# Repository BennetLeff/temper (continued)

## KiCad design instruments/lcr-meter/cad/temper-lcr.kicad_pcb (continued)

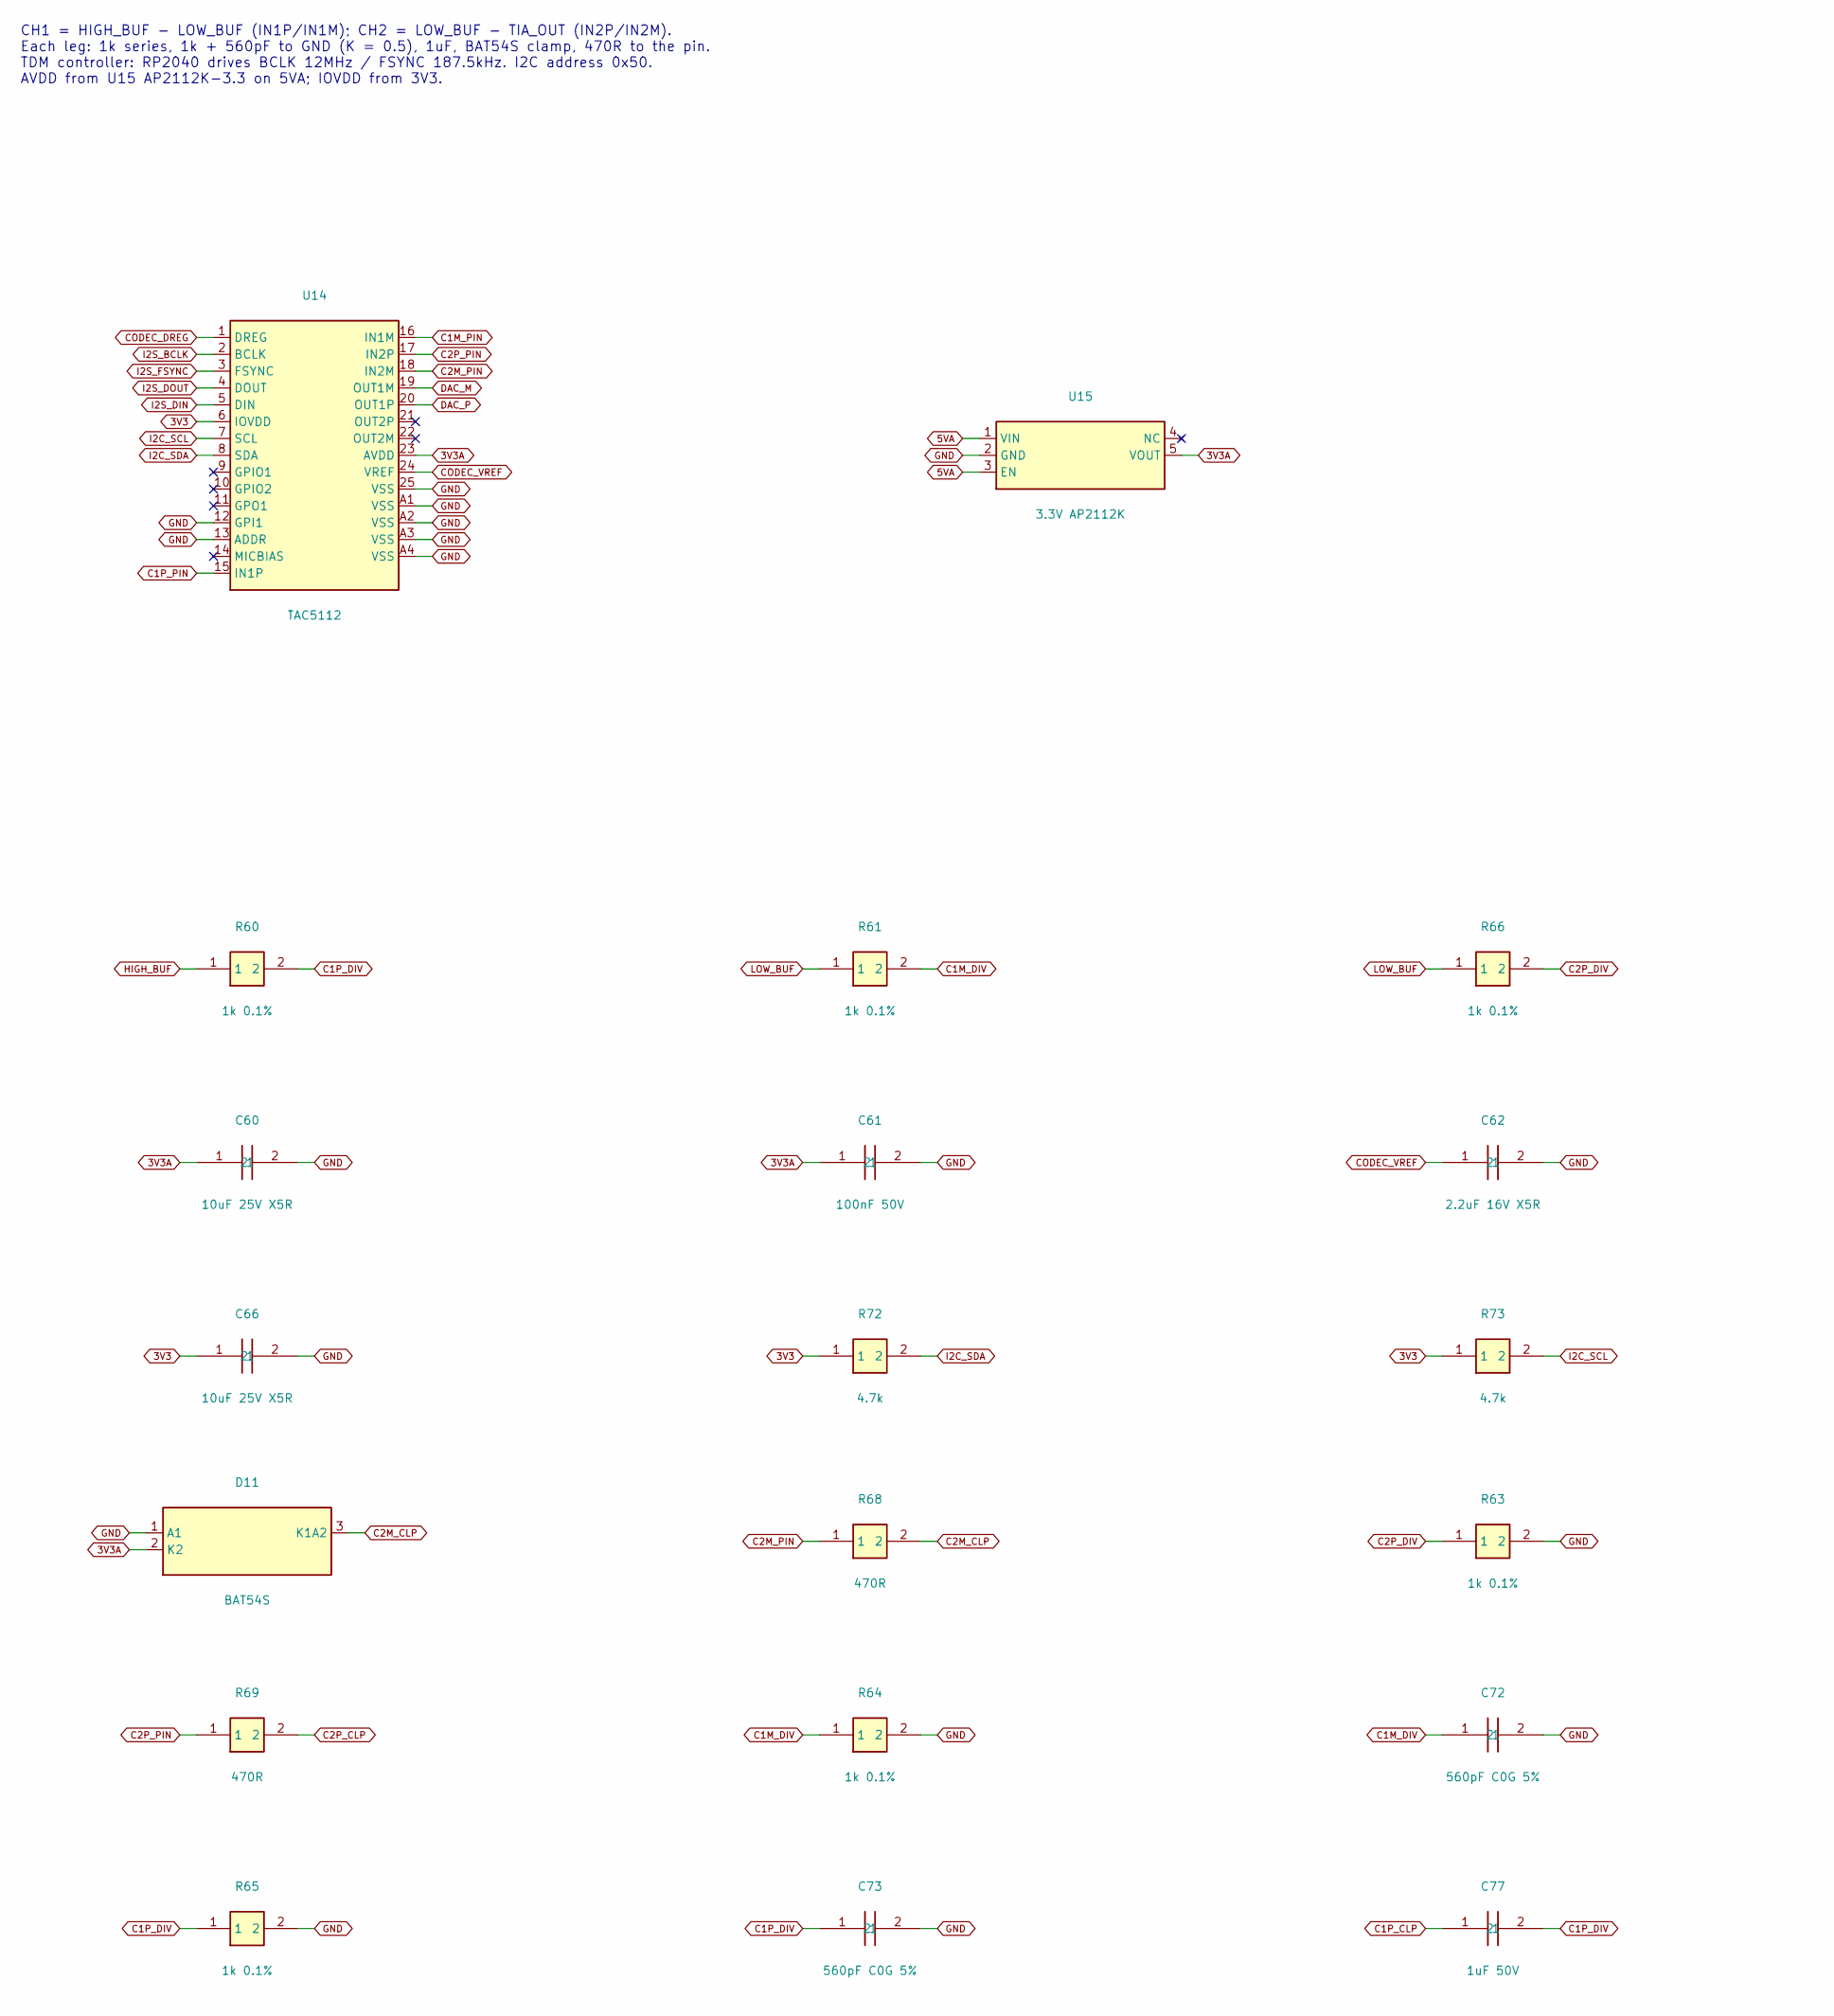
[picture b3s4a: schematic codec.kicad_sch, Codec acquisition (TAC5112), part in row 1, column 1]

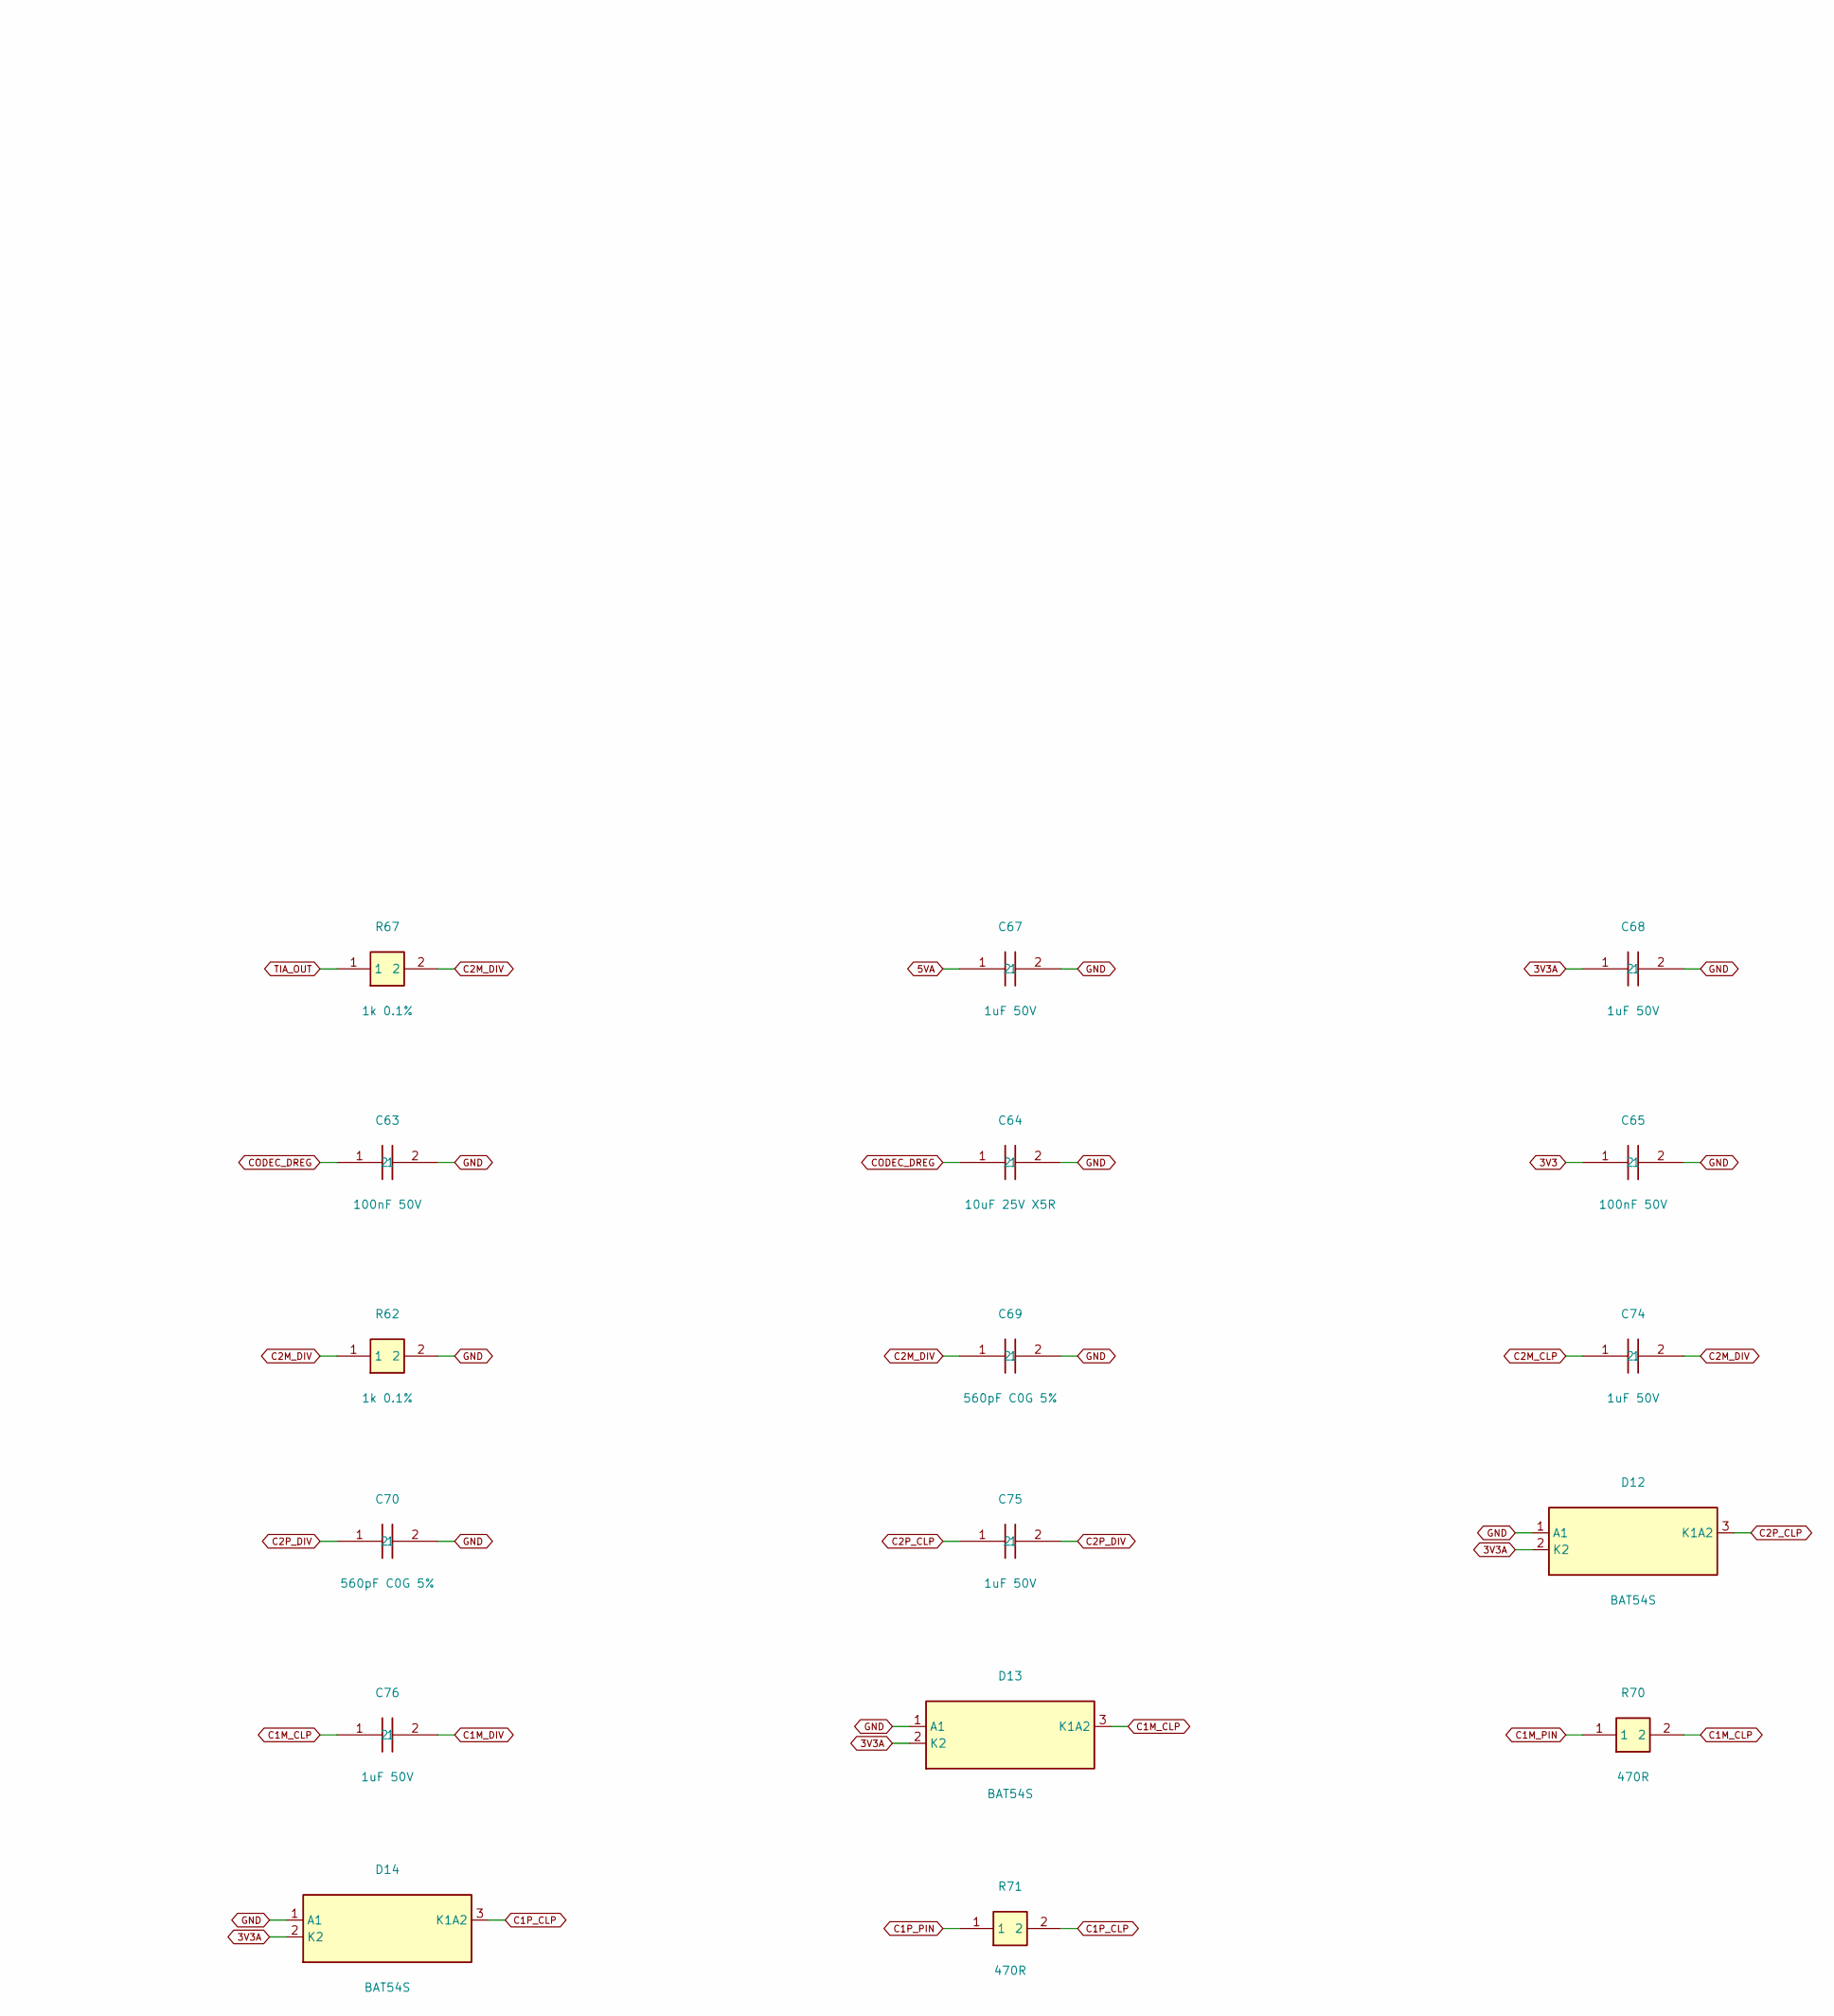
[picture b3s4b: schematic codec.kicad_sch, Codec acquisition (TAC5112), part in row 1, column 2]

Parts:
C60, C64, C66: 10uF 25V X5R; C_0805_2012Metric; MPN CL21A106KAYNNNE; LCSC C15850
C61, C63, C65: 100nF 50V; C_0603_1608Metric; MPN CC0603KRX7R9BB104; LCSC C14663
C62: 2.2uF 16V X5R; C_0603_1608Metric; MPN CL10A225KO8NNNC; LCSC C23630
C67, C68, C74, C75, C76, C77: 1uF 50V; C_0805_2012Metric; MPN CL21B105KBFNNNE; LCSC C28323
C69, C70, C72, C73: 560pF C0G 5%; C_0603_1608Metric; MPN CC0603JRNPO9BN561; LCSC C107054
D11, D12, D13, D14: BAT54S; SOT-23; MPN BAT54S; LCSC C7420333
R60, R61, R62, R63, R64, R65, R66, R67: 1k 0.1%; R_0603_1608Metric; MPN RT0603BRD071KL; LCSC C110776
R68, R69, R70, R71: 470R; R_0603_1608Metric; MPN 0603WAF4700T5E; LCSC C23179
R72, R73: 4.7k; R_0603_1608Metric; MPN 0603WAF4701T5E; LCSC C23162
U14: TAC5112; TI_RGE0024R_VQFN-24-1EP_4x4mm_P0.5mm_EP2.1mm_CornerPads; MPN TAC5112IRGER; LCSC C44853692
U15: 3.3V AP2112K; SOT-23-5; MPN AP2112K-3.3TRG1; LCSC C51118

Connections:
3V3: C65.1, C66.1, R72.1, R73.1, U14.6 (IOVDD); also elsewhere on the board
3V3A: C60.1, C61.1, C68.1, D11.2 (K2), D12.2 (K2), D13.2 (K2), D14.2 (K2), U14.23 (AVDD), U15.5 (VOUT)
5VA: C67.1, U15.1 (VIN), U15.3 (EN); also elsewhere on the board
C1M_CLP: C76.1, D13.3 (K1A2), R70.2
C1M_DIV: C72.1, C76.2, R61.2, R64.1
C1M_PIN: R70.1, U14.16 (IN1M)
C1P_CLP: C77.1, D14.3 (K1A2), R71.2
C1P_DIV: C73.1, C77.2, R60.2, R65.1
C1P_PIN: R71.1, U14.15 (IN1P)
C2M_CLP: C74.1, D11.3 (K1A2), R68.2
C2M_DIV: C69.1, C74.2, R62.1, R67.2
C2M_PIN: R68.1, U14.18 (IN2M)
C2P_CLP: C75.1, D12.3 (K1A2), R69.2
C2P_DIV: C70.1, C75.2, R63.1, R66.2
C2P_PIN: R69.1, U14.17 (IN2P)
CODEC_DREG: C63.1, C64.1, U14.1 (DREG)
CODEC_VREF: C62.1, U14.24 (VREF)
DAC_M: U14.19 (OUT1M); also elsewhere on the board
DAC_P: U14.20 (OUT1P); also elsewhere on the board
GND: C60.2, C61.2, C62.2, C63.2, C64.2, C65.2, C66.2, C67.2, C68.2, C69.2, C70.2, C72.2, C73.2, D11.1 (A1), D12.1 (A1), D13.1 (A1), D14.1 (A1), R62.2, R63.2, R64.2, R65.2, U14.12 (GPI1), U14.13 (ADDR), U14.25 (VSS), U14.A1 (VSS), U14.A2 (VSS), U14.A3 (VSS), U14.A4 (VSS), U15.2 (GND); also elsewhere on the board
HIGH_BUF: R60.1; also elsewhere on the board
I2C_SCL: R73.2, U14.7 (SCL); also elsewhere on the board
I2C_SDA: R72.2, U14.8 (SDA); also elsewhere on the board
I2S_BCLK: U14.2 (BCLK); also elsewhere on the board
I2S_DIN: U14.5 (DIN); also elsewhere on the board
I2S_DOUT: U14.4 (DOUT); also elsewhere on the board
I2S_FSYNC: U14.3 (FSYNC); also elsewhere on the board
LOW_BUF: R61.1, R66.1; also elsewhere on the board
TIA_OUT: R67.1; also elsewhere on the board

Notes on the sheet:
CH1 = HIGH_BUF - LOW_BUF (IN1P/IN1M); CH2 = LOW_BUF - TIA_OUT (IN2P/IN2M). Each leg: 1k series, 1k + 560pF to GND (K = 0.5), 1uF, BAT54S clamp, 470R to the pin. TDM controller: RP2040 drives BCLK 12MHz / FSYNC 187.5kHz. I2C address 0x50. AVDD from U15 AP2112K-3.3 on 5VA; IOVDD from 3V3.

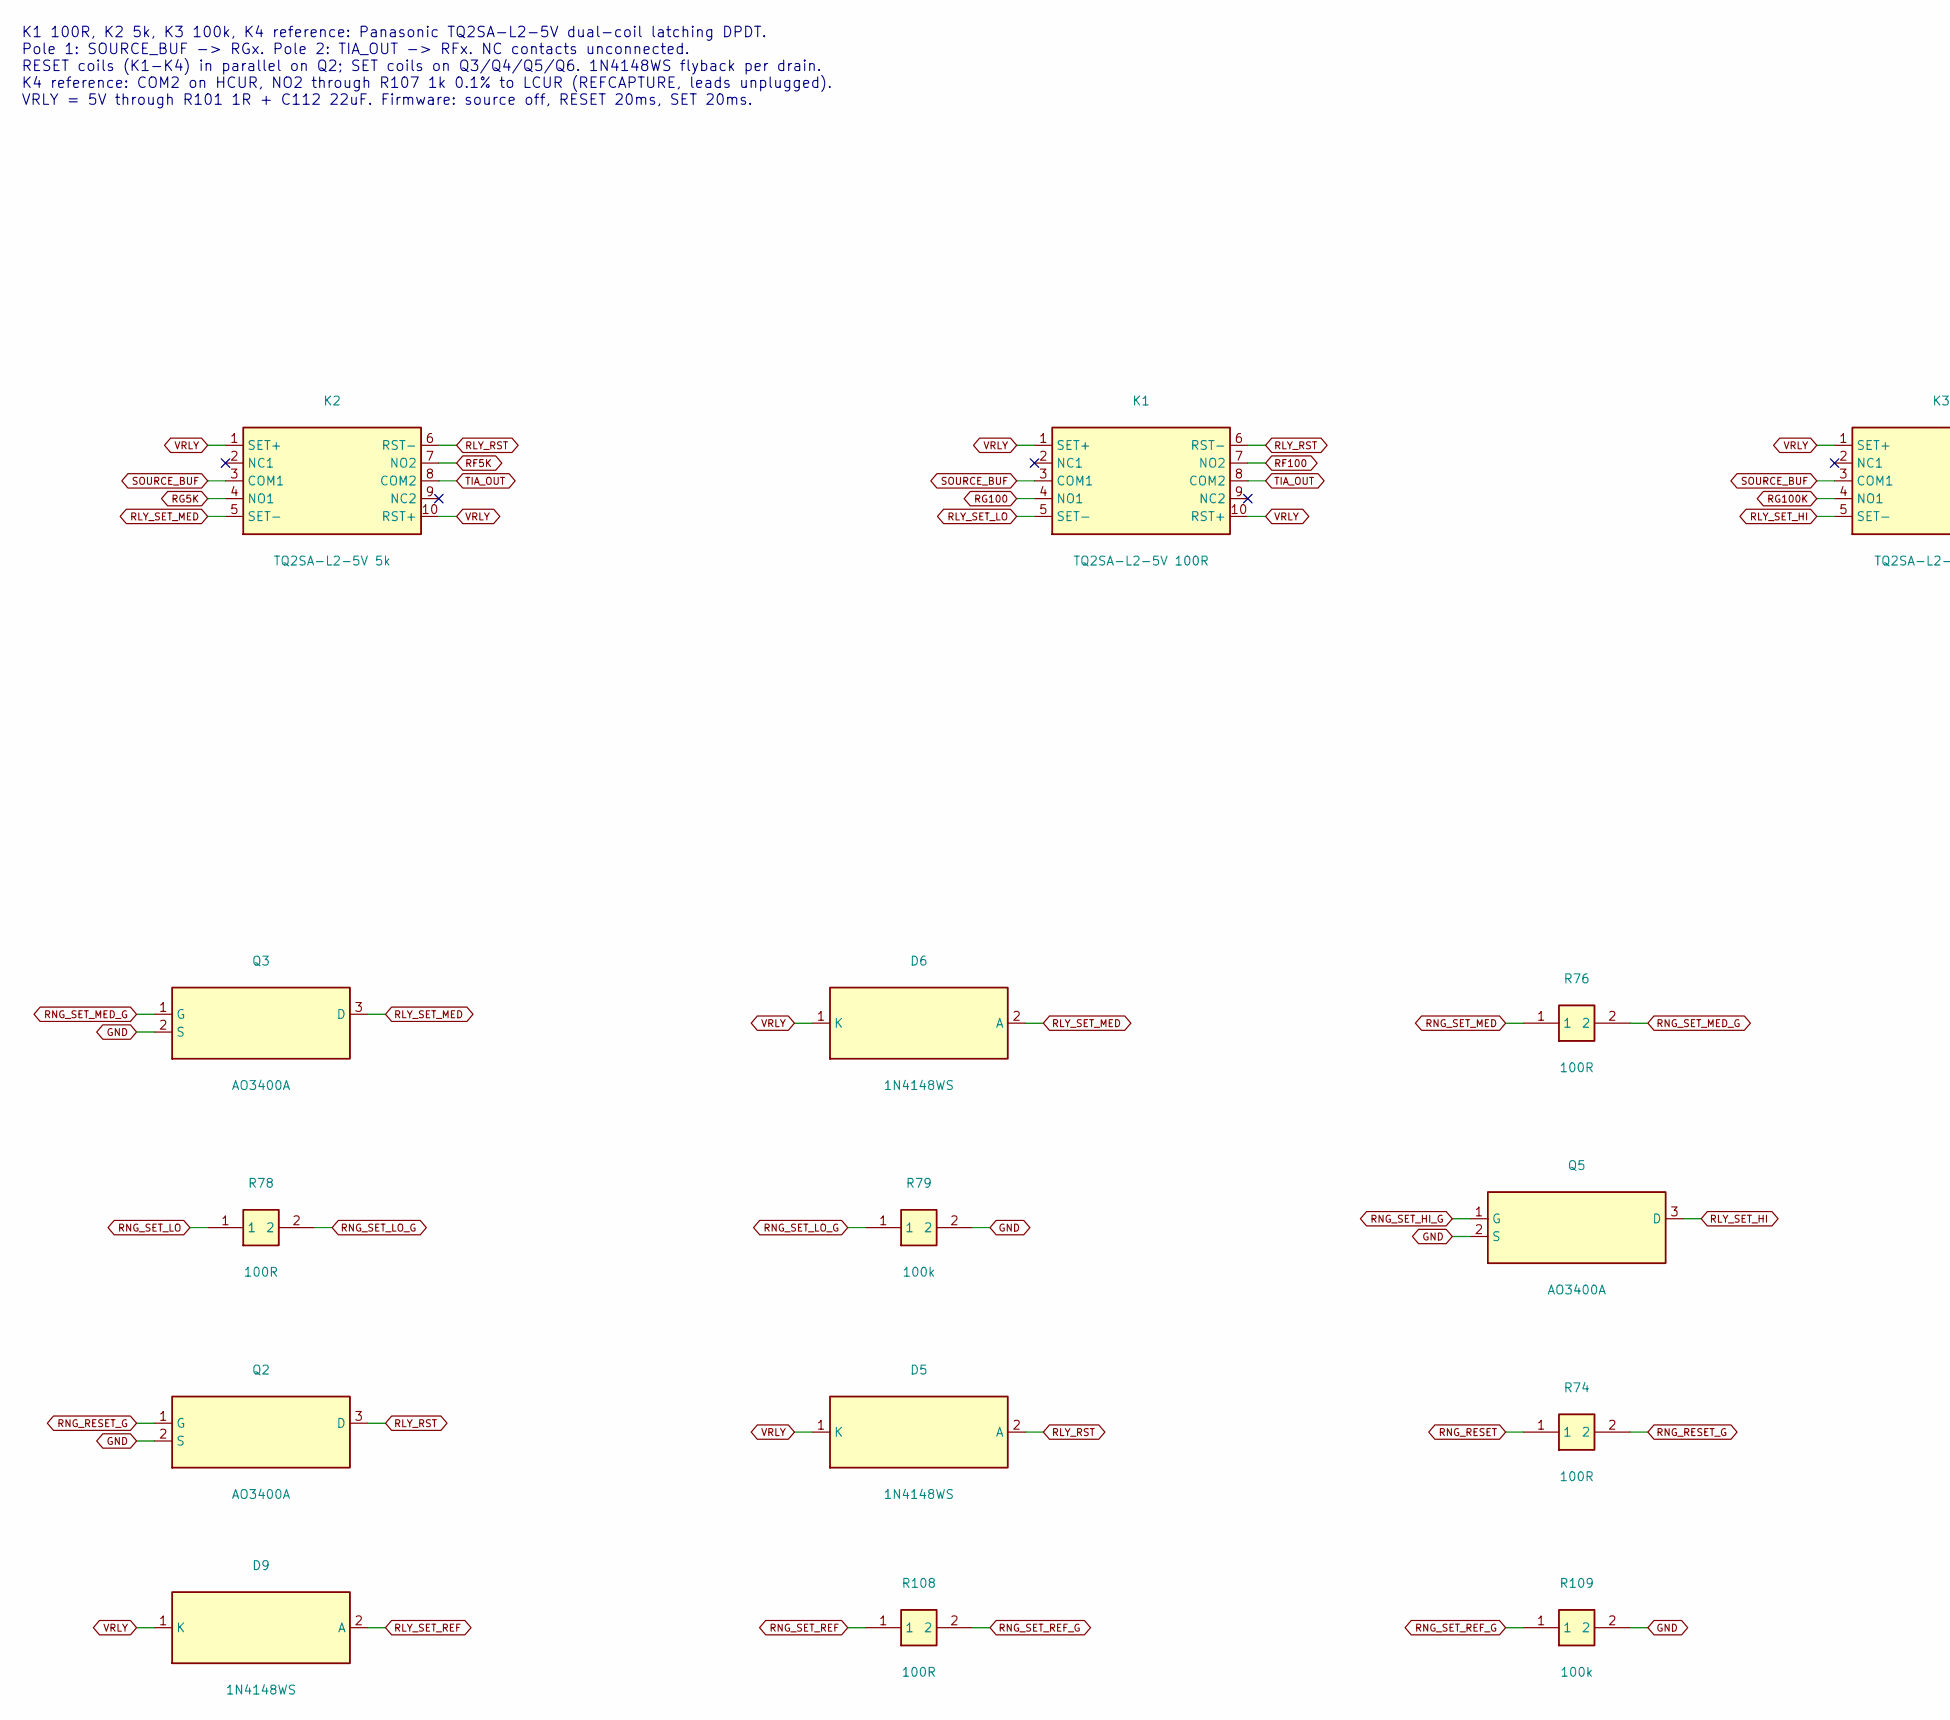
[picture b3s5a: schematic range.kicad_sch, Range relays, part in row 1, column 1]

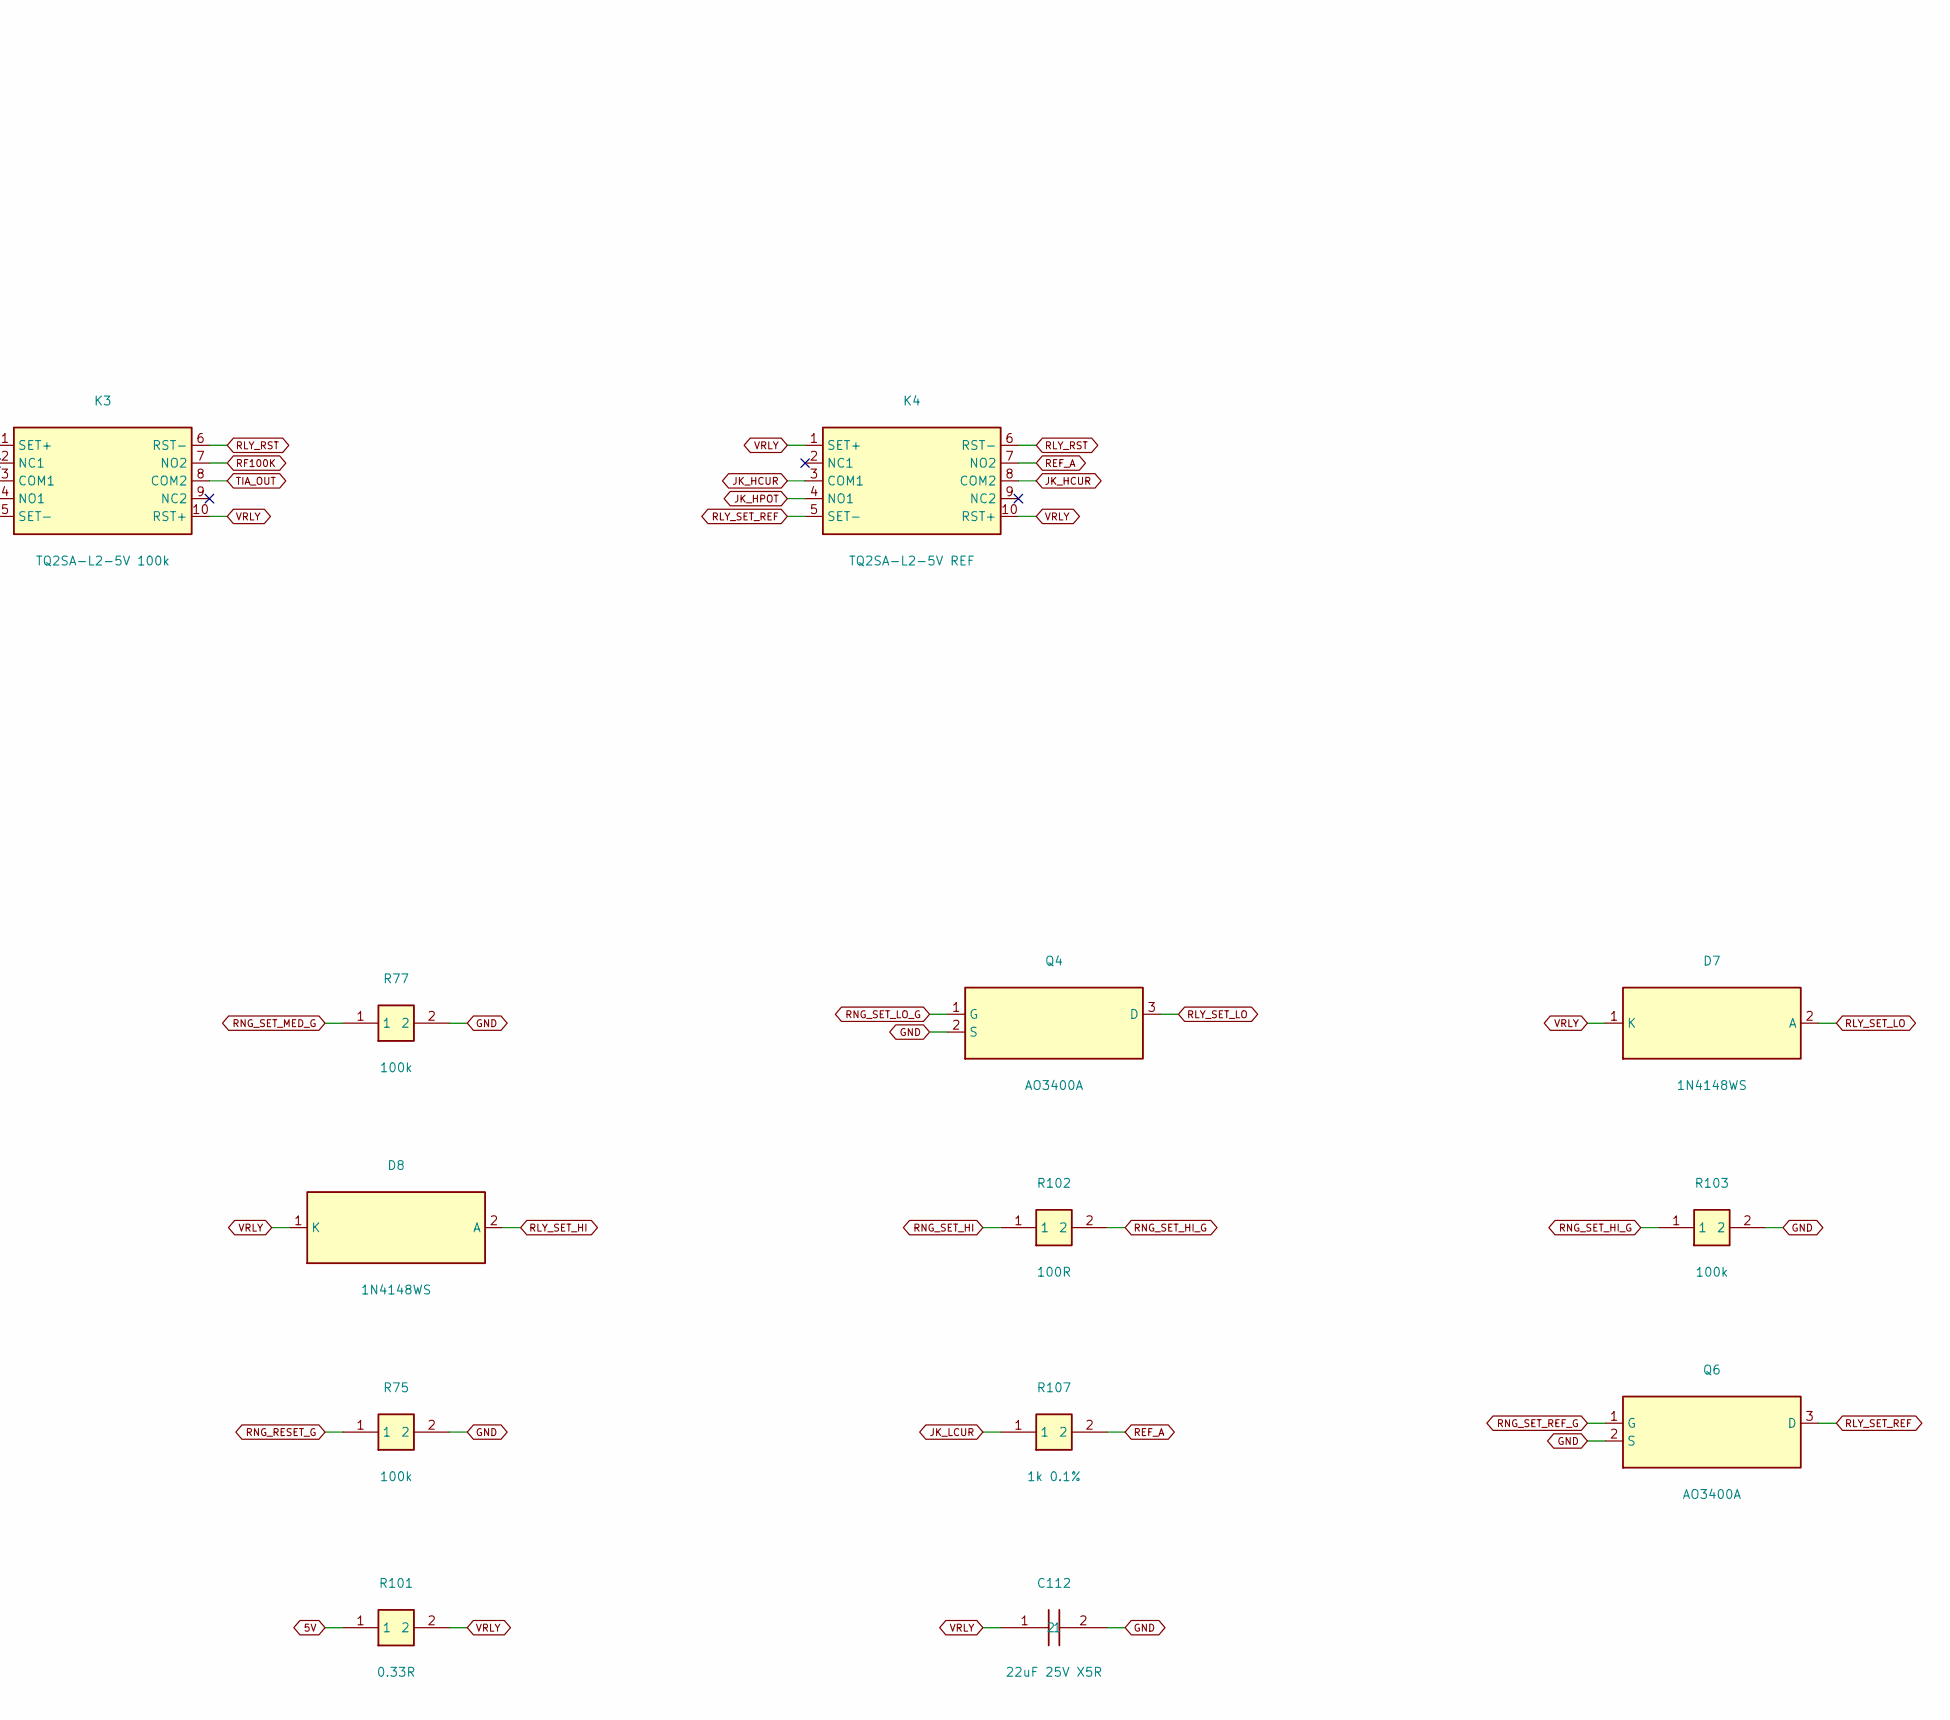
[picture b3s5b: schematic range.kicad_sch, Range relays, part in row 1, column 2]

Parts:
C112: 22uF 25V X5R; C_1206_3216Metric; MPN CL31A226KAHNNNE; LCSC C12891
D5, D6, D7, D8, D9: 1N4148WS; D_SOD-323; MPN 1N4148WS; LCSC C2128
K1: TQ2SA-L2-5V 100R; Relay_DPDT_Panasonic_TQ2SA_SMD; MPN TQ2SA-L2-5V-Z; LCSC C2684450
K2: TQ2SA-L2-5V 5k; Relay_DPDT_Panasonic_TQ2SA_SMD; MPN TQ2SA-L2-5V-Z; LCSC C2684450
K3: TQ2SA-L2-5V 100k; Relay_DPDT_Panasonic_TQ2SA_SMD; MPN TQ2SA-L2-5V-Z; LCSC C2684450
K4: TQ2SA-L2-5V REF; Relay_DPDT_Panasonic_TQ2SA_SMD; MPN TQ2SA-L2-5V-Z; LCSC C2684450
Q2, Q3, Q4, Q5, Q6: AO3400A; SOT-23; MPN AO3400A; LCSC C20917
R74, R76, R78, R102, R108: 100R; R_0603_1608Metric; MPN 0603WAF1000T5E; LCSC C22775
R75, R77, R79, R103, R109: 100k; R_0603_1608Metric; MPN 0603WAF1003T5E; LCSC C25803
R101: 0.33R; R_0603_1608Metric; MPN 0603WAF330LT5E; LCSC C23410
R107: 1k 0.1%; R_0603_1608Metric; MPN RT0603BRD071KL; LCSC C110776

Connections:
5V: R101.1; also elsewhere on the board
GND: C112.2, Q2.2 (S), Q3.2 (S), Q4.2 (S), Q5.2 (S), Q6.2 (S), R75.2, R77.2, R79.2, R103.2, R109.2; also elsewhere on the board
JK_HCUR: K4.3 (COM1), K4.8 (COM2); also elsewhere on the board
JK_HPOT: K4.4 (NO1); also elsewhere on the board
JK_LCUR: R107.1; also elsewhere on the board
REF_A: K4.7 (NO2), R107.2
RF5K: K2.7 (NO2); also elsewhere on the board
RF100: K1.7 (NO2); also elsewhere on the board
RF100K: K3.7 (NO2); also elsewhere on the board
RG5K: K2.4 (NO1); also elsewhere on the board
RG100: K1.4 (NO1); also elsewhere on the board
RG100K: K3.4 (NO1); also elsewhere on the board
RLY_RST: D5.2 (A), K1.6 (RST-), K2.6 (RST-), K3.6 (RST-), K4.6 (RST-), Q2.3 (D); also elsewhere on the board
RLY_SET_HI: D8.2 (A), K3.5 (SET-), Q5.3 (D); also elsewhere on the board
RLY_SET_LO: D7.2 (A), K1.5 (SET-), Q4.3 (D); also elsewhere on the board
RLY_SET_MED: D6.2 (A), K2.5 (SET-), Q3.3 (D); also elsewhere on the board
RLY_SET_REF: D9.2 (A), K4.5 (SET-), Q6.3 (D); also elsewhere on the board
RNG_RESET: R74.1; also elsewhere on the board
RNG_RESET_G: Q2.1 (G), R74.2, R75.1
RNG_SET_HI: R102.1; also elsewhere on the board
RNG_SET_HI_G: Q5.1 (G), R102.2, R103.1
RNG_SET_LO: R78.1; also elsewhere on the board
RNG_SET_LO_G: Q4.1 (G), R78.2, R79.1
RNG_SET_MED: R76.1; also elsewhere on the board
RNG_SET_MED_G: Q3.1 (G), R76.2, R77.1
RNG_SET_REF: R108.1; also elsewhere on the board
RNG_SET_REF_G: Q6.1 (G), R108.2, R109.1
SOURCE_BUF: K1.3 (COM1), K2.3 (COM1), K3.3 (COM1); also elsewhere on the board
TIA_OUT: K1.8 (COM2), K2.8 (COM2), K3.8 (COM2); also elsewhere on the board
VRLY: C112.1, D5.1 (K), D6.1 (K), D7.1 (K), D8.1 (K), D9.1 (K), K1.1 (SET+), K1.10 (RST+), K2.1 (SET+), K2.10 (RST+), K3.1 (SET+), K3.10 (RST+), K4.1 (SET+), K4.10 (RST+), R101.2; also elsewhere on the board

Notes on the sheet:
K1 100R, K2 5k, K3 100k, K4 reference: Panasonic TQ2SA-L2-5V dual-coil latching DPDT. Pole 1: SOURCE_BUF -> RGx. Pole 2: TIA_OUT -> RFx. NC contacts unconnected. RESET coils (K1-K4) in parallel on Q2; SET coils on Q3/Q4/Q5/Q6. 1N4148WS flyback per drain. K4 reference: COM2 on HCUR, NO2 through R107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
